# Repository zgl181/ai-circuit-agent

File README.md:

# AI Agent 电路板设计

> **给 AI 一句话，产出一块板子。**
> 输入自然语言需求（如「设计一个 LED 闪烁电路，1 个 LED、1 个限流电阻、1 个轻触按钮、1 个电池座」），
> 自动产出 **BOM 元件清单 + 引脚级网表 + KiCad 8 可直接打开的原理图**。

个人课程大作业（8 周项目制） · Python 3.10+ / KiCad 8 / LLM（OpenAI 兼容接口）

---

## 效果

一句需求 → 原理图 → PCB 全链路产物：

| 产物 | 说明 |
|---|---|
| `outputs/design.json` | 结构化设计：`{board, components[], nets[]}`（BOM + 引脚级连接） |
| `outputs/design.net` | KiCad 标准网表（可直接给 pcbnew 做布局） |
| `outputs/design.kicad_sch` | KiCad 8 原理图，**双击即可打开** |
| `outputs/design.svg` | 原理图预览图（用于网页展示 / 自动校验） |
| `outputs/design.kicad_pcb` | KiCad 8 **PCB 板文件**：真实官方封装 + 自动布局 + 双层走线 + 两层 GND 铺铜 |
| `outputs/board_routes.json` | 自动布线结果（每条走线的网络、层、折点、过孔） |
| `outputs/drc_report_summary.json` | DRC 闭环报告：每轮违规数 / 未连接数下降曲线与最终统计 |
| `outputs/pcb.svg` / `pcb_preview.png` | PCB 顶层装配视图（隐藏铜皮，便于看清元件与走线） |

原理图和 PCB 都会**自动通过 `kicad-cli` 反向校验**：前者反导网表逐引脚比对，后者跑 DRC 并用报告反向驱动布线，确认不是"只画了好看的线"。

> **W8 设计报告**：[`AI Agent 电路板设计-设计报告.docx`](./AI%20Agent%20电路板设计-设计报告.docx)——含封面、目录、页码、两张预览图与全部自检数据。正文九章 + 两个附录，覆盖需求架构、基础五步、进阶 PCB/DRC 闭环、六项自检、F1 语义错误案例、过程管理与 AI 使用声明。

## 功能特性

- **自然语言 → 结构化设计**：LLM 输出固定 JSON（BOM + 网表），带自检（位号引用一致性）
- **生成真实可用的 KiCad 8 原理图**：内嵌真实符号定义，文件自包含，无需额外库表
- **自适应论文式排版**：按元件类型与连接关系动态分组，只画实际用到的功能框（**空组一律不画**），框贴合内容、整体在 A4 内居中铺满；Arduino 完整版沿用人工验收的固定五分区。一键生成和每次微调都会重新排版，始终给出最好看的版面
- **正交自动布线 + 网络名标签**：先横后竖连线，网络名贴在导线中点
- **PCB 自动布局布线（进阶）**：26 个元件全部映射到 KiCad 官方封装，按 5 个功能分区 shelf-packing 排布，35 个网络逐焊盘绑定；双层 0.5mm 网格 A* 自动布线，自动打过孔换层
- **DRC 闭环（进阶）**：`kicad-cli pcb drc --format json` 报出「项目之间的连接缺失」→ 解析两个焊盘的精确坐标与网络名 → 自动补线 → 重跑 DRC，逐轮让未连接项下降
- **GND 铺铜**：F.Cu / B.Cu 全板敷铜，自动避让其它网络，一次性连通所有地焊盘
- **本地网页界面**：零前端框架，原理图 / PCB 预览一键切换，可下载 `.kicad_pcb`
- **MongoDB 后端（可选）**：设计历史、多用户登录、LLM 结果缓存、多 Agent 共享状态；**未安装 mongod 时自动退化为内存版 mongomock，照样能跑**
- **离线兜底（平台抖动也不停工）**：学校 LLM 不可达时 5 秒内自动切到内置模板（LED 闪烁 / 双 LED 流水灯 / 电池开关灯 / ATmega 最小系统），一键生成照常出图
- **交互修正（基础第五步）**：生成后可在结果页"追加要求"框直接说「再加一个 10k 电阻」「把 LED 换成绿色」「去掉按钮」，在当前电路上增删改并**自动重新排版**；LLM 不可用时走本地规则解析，照样能用
- **对话工作台（推荐，`/chat`）**：仿对话助手界面——**每次新建对话 = 一份独立电路**；第一条消息生成，之后在同一对话里反复改图，每轮都有快照。**不同对话之间完全隔离**：在 A 里加电阻、改颜色，B 新生成的仍是干净原始电路，互不污染
- **六项一键自检**：网表一致性 / ERC / 排版几何 / 导线穿模 / PCB 与 DRC 闭环 / 电源语义

## 技术架构

```
            自然语言需求
                 │
                 ▼
   scripts/design_agent.py  ── 5s 探测学校平台
                 │             ├─ 可达：LLM 输出严格 JSON（BOM + nets）
                 │             └─ 不可达：local_design.py 内置模板兜底
                 ▼
          design.json  {board, components[], nets[]}
          ┌──────┴───────────────────────┐
          ▼                              ▼
 scripts/kicad_net.py            scripts/kicad_sch.py
   → design.net (KiCad 网表)       → design.kicad_sch (KiCad 8 原理图)
                                          │
                                          ▼
                                   kicad-cli sch export svg  → design.svg
                                   kicad-cli sch export netlist → 连通性校验
```

网页层 `scripts/app.py` 把上面整条管线包成 HTTP 接口，`scripts/db.py` 提供 MongoDB 存储。

## 项目结构

```
.
├── scripts/
│   ├── design_agent.py     # 自然语言 -> BOM + 网表 JSON（真调 LLM）
│   ├── kicad_net.py        # JSON -> KiCad 网表 .net
│   ├── kicad_sch.py        # JSON -> KiCad 8 原理图 .kicad_sch（内嵌符号 + 正交布线）
│   ├── kicad_pcb.py        # JSON -> KiCad 8 PCB（官方封装 + 分区布局 + 走线 + 铺铜）
│   ├── drc_loop.py         # DRC 报告 -> 双层 A* 自动补线 -> 重跑 DRC 的闭环编排
│   ├── verify_schematic.py # 六项一键自检（原理图 A–D + PCB/DRC E + 电源语义 F）
│   ├── llm_client.py       # LLM 客户端（读取 .env，5s 可达性探测 + 重试）
│   ├── local_design.py     # LLM 不可达时的内置电路模板兜底
│   ├── local_refine.py     # 交互修正：离线规则解析「增/删/改」增量要求
│   ├── templates/          # 内置模板（已验收的 ATmega 最小系统 design.json）
│   ├── db.py               # MongoDB 数据层（自动退化 mongomock）
│   ├── app.py              # 本地网页服务（注册/登录/生成/历史/共享状态）
│   ├── web/index.html      # 旧版单页界面（/）
│   └── web/chat.html       # 对话工作台（/chat，推荐）
├── outputs/                # 生成产物（示例）
├── requirements.txt
├── .env.example            # 密钥模板（真实 .env 不进仓库）
├── 启动界面.bat             # Windows 一键启动网页界面
└── README.md
```

## 环境要求

- Python **3.10+**
- KiCad **8.x**（需要 `kicad-cli` 与符号库 `share/kicad/symbols`）
- LLM API：任何 **OpenAI 兼容**接口（本项目默认接学校平台）
- MongoDB **（可选）**：不装也能跑，走 mongomock 兜底

## 安装

```bash
git clone <你的仓库地址>
cd <仓库目录>

python -m venv .venv
.venv\Scripts\activate            # Windows
# source .venv/bin/activate       # macOS / Linux

pip install -r requirements.txt

# 配置密钥：复制模板后填写
copy .env.example .env             # Windows
# cp .env.example .env             # macOS / Linux
```

### `.env` 说明

```ini
LLM_API_KEY=你的密钥
LLM_BASE_URL=https://你的平台地址/v1
LLM_MODEL=你的模型名
```

### KiCad 路径（可选覆盖）

默认使用 Windows KiCad 8 安装路径；若你的安装位置不同，用环境变量覆盖即可：

```bash
set KICAD_SYM_DIR=D:\KiCad\8.0\share\kicad\symbols
set KICAD_CLI=D:\KiCad\8.0\bin\kicad-cli.exe
```

## 运行

### 方式一：命令行（三段管线）

```bash
# 1) 自然语言 -> 设计 JSON
python scripts/design_agent.py "设计一个 LED 闪烁电路，包含 1 个 LED、1 个限流电阻、1 个轻触按钮、1 个 2 节电池座"

# 2) JSON -> 网表
python scripts/kicad_net.py outputs/design.json outputs/design.net

# 3) JSON -> 原理图
python scripts/kicad_sch.py outputs/design.json outputs/design.kicad_sch
```

### 方式一（续）：PCB 与 DRC 闭环（进阶）

PCB 用 `pcbnew` Python API，**必须用 KiCad 自带的 Python 运行**（项目 `.venv` 里没有 pcbnew）：

```bash
# 4) JSON -> PCB（真实封装、分区布局、GND 铺铜）
"C:/Users/24013/Desktop/工具/bin/python.exe" scripts/kicad_pcb.py

# 5) DRC 闭环：自动布线 + 迭代校验，一步到位（内部会反复调用 4）
"C:/Users/24013/Desktop/工具/bin/python.exe" scripts/drc_loop.py --max-iter 7

# 6) 六项一键自检
python scripts/verify_schematic.py
```

KiCad 路径不同可用环境变量覆盖：`KICAD_FP_DIR`（封装库）、`KICAD_CLI`（命令行工具）。
`drc_loop.py` 会在最后一轮自动起一个独立进程填充铜皮，避开 pcbnew 在同一进程反复 zone fill 的段错误。

### 方式二：网页界面（推荐）

```bash
# 双击 启动界面.bat ；或手动：
.venv\Scripts\python.exe scripts\app.py
```

浏览器打开 <http://localhost:8765>：

1. 输入需求（或点示例）→ 点「生成原理图」
2. 页面直接显示 BOM 表格、网表、原理图预览
3. 可下载 `.kicad_sch` / `.net` / `.json`
4. 注册登录后，设计自动存入「我的设计历史」，可回看载入
5. 相同需求二次生成会**命中 LLM 缓存**，不再重复调用模型
6. 学校平台连不上时自动用内置模板出图（约 5 秒），不报错、不用改配置
7. **追加要求**：生成结果下方有「追加要求」框，输入「再加一个 10k 电阻」「去掉按钮」「把 R1 改成 1k」等，点「应用修改并重新排版」即可在当前电路上迭代，无需重写整段需求

> **对话工作台**（推荐）：访问 <http://localhost:8765/chat>。左侧「+ 新建对话」开一份独立电路，第一条消息生成，后续消息都在本对话里改图；每轮消息附**原理图 / PCB 双预览**（可切换）与 JSON / 网表 / `.kicad_sch` / `.kicad_pcb` / SVG 下载。生成过程有分阶段状态提示，不会让人误以为卡住。不同对话各自保存 design，互不影响——适合"一个需求一个对话、随便改"的用法。
>
> **对话记录持久化**：对话存在 `.workbuddy/chat_store.json`（独立于 MongoDB/mongomock），**服务重启、刷新页面都不丢**；点左侧「×」可删除单个对话。旧版单页仍在 `/`。

## MongoDB 后端（可选）

- **不装 mongod**：`db.py` 连不上本地 `mongodb://localhost:27017` 时自动使用 `mongomock`（内存），功能齐全但重启即清空。
- **装了 mongod**：启动服务时自动切到 `real` 模式，数据持久化。

### 本机已部署（便携版，无需管理员权限）

MongoDB 8.0 便携版已下载解压到本机，普通用户即可运行：

- 程序：`C:\Users\24013\Desktop\工具\mongodb\mongodb-win32-x86_64-windows-8.0.0\bin\mongod.exe`
- 数据目录：`C:\Users\24013\Desktop\工具\mongodb-data`（重启后数据仍在）
- 默认监听 `127.0.0.1:27017`，仅本机访问

启动方式（二选一）：

- **双击 `启动界面.bat`（推荐）**：先拉起 MongoDB，等几秒再开网页界面，一条龙。
- **双击 `start-mongo.bat`**：只启动 MongoDB（不启网页），便于单独调试。

> 装好并运行后，`scripts/db.py` 会自动从 `mongomock`（内存）切到 `real`（真 MongoDB），无需改任何代码。判断当前模式：启动后访问网页、注册/生成任意一次，或在 `scripts/` 下执行
> `.venv\Scripts\python.exe -c "import db; print(db.mode())"` 会打印 `real`。

集合设计（数据库 `circuit_agent`）：

| 集合 | 用途 |
|---|---|
| `users` | 账号（加盐 SHA-256 存密码哈希） |
| `sessions` | 登录 token |
| `designs` | 设计历史（按 owner 隔离） |
| `cache` | LLM 结果缓存（按 prompt 的 SHA-256 命中） |
| `agent_state` | 多 Agent 共享状态（键值） |

## 已验证

示例设计为 **Arduino 最小系统板**（ATmega328P-PU DIP-28 + CH340G USB 转串口），
26 个元件 / 35 个网络。一键自检：

```bash
python scripts/verify_schematic.py
```

该脚本校验六项，全部通过才返回退出码 0（可直接用于答辩演示或 CI）：

| 检查 | 方法 | 当前结果 |
| --- | --- | --- |
| A. 网表一致性 | `kicad-cli sch export netlist` 反导出的网表与 `design.json` 逐网络、逐引脚比对；并检测同一引脚落入多个网络（短路） | 35/35 一致，0 短路 |
| B. 电气规则 | 解析 `erc.txt`，统计 `; error` | 0 error（144 条为 `endpoint_off_grid` / `lib_symbol_issues` 提示，不影响电气） |
| C. 排版几何 | 解析 `.kicad_sch` **内嵌符号的真实引脚坐标**，检查元件重叠、标签压元件、标签互相叠字、超出 A4 图框 | 26 元件 / 108 标签，4 项均为 0 |
| D. 导线不穿模 | 逐段采样导线，检查其中段是否穿过任何元件本体（两端各跳过 4.5mm 引脚区） | 112 段导线，穿模 0 段 |
| E. PCB / DRC 闭环 | 检查板文件、走线、闭环报告齐备；设计规则违规必须为 0，且未连接项须比首轮明显下降 | 违规 0，未连接 58 → 22（223 段走线 / 25 过孔） |
| F. 电源语义 | 直接校验 `design.json` 的**供电逻辑**：保护/限流器件不得跨接电源与地，保险丝必须串联在两个不同的电源网络之间 | F1 = `USB_VBUS → +5V` 串联正确，异常跨接 0 |

> **为什么单列 F 项**：A–E 验的是「生成文件是否忠实于设计 JSON」。如果 LLM 一开始就把保险丝写成
> `+5V → GND`，图画得再准、ERC 与 DRC 也照样全绿。本项对设计意图做独立规则判断；
> 已用回归测试验证：把 F1 改回旧接法时 F 项会立即 FAIL。

原理图为 A4 横向（`viewBox = 297×210mm`），采用**论文插画式**版面：

- **5 个虚线功能分区 + 加粗小标题**（① 电源输入、② USB-UART/CH340G、③ MCU 核心、④ 去耦与 I/O 排针、⑤ 状态指示与复位），元件只在自己的框内排布，读图不必全屏搜索。
- **主控是左右对称的 DIP-28**：左侧 pin1–14、右侧 pin28–15，引脚名按数据手册（PC6/RESET、PD0/RXD…）标注，网络标签在两侧各排成整齐一列。官方库 `ATmega328P-P` 把 23 个脚全画在右侧，这里用自包含的对称符号替换（不动本机库）。
- **LED 支路是真正的串联**：限流电阻改用横放符号，与 LED 引脚同向，`D13 → R3 → LED_D13 → D2 → GND` 画成一条干净的水平线；中间的网络名标签抬到导线上方 1.8mm，用一小段竖线挂接（水平导线在分支点拆成两段以保证电气连通），文字不再被导线穿过。不再是"一条线穿过电阻本体"。
- 其余符号直接嵌入 KiCad 官方库的**原始图形**（电容双板、电阻、晶振、开关、排针等），不是空白矩形框；所有导线均为短正交直线 stub（无斜线），网络标签朝元件外侧展开，位号/数值文字按真实符号高度紧贴本体。右下角标题栏未被压住。

**两种排版路线**：`build_sch()` 先判断是否为 Arduino 完整版（ATmega328P + CH340G 且元件数 ≥18）——是则沿用上面这套人工验收的固定五分区（保证已交付产物零回归）；否则走 `adaptive_layout()`：按元件类型 + 连接关系动态分组、**只画实际有元件的框**，框大小贴合内容、整体在 A4 可用区（Y ≤168mm，避开标题栏）内居中铺满，列数从 1 到 4 自动扩展以适配不同规模。这样从 2 元件到 26 元件，一键生成和每次微调都能得到没有空框、不压标题栏的版面。回归验收：`2 / 6 / 12 / 26` 元件四种规模均渲染通过，官方版电气与几何事实与交付产物完全一致。

`kicad-cli sch export svg` 可正常导出，渲染预览见 `outputs/schematic_preview.png`。

## PCB 与 DRC 闭环（进阶项）

板框 140×62mm，26 个元件全部使用 KiCad 8 **官方封装**（DIP-28 / SOIC-16 / HC-49 / 0603 / Micro-USB / 排针等），
按原理图的 5 个功能分区做 shelf-packing 自动布局，35 个网络逐焊盘绑定（112 处，无遗漏）。

**闭环工作方式** —— 不是"画完线再跑一次 DRC"，而是让 DRC 报告反过来驱动布线：

1. `kicad-cli pcb drc --format json` 把「项目之间的连接缺失」逐条列出，每条都带**两个端点的精确坐标与网络名**；
2. 双层 0.5mm 网格 A* 在焊盘和已布走线之间找正交通路，其它网络一律视为障碍，必要时自动打过孔换层；
3. 把新走线写回板子，重跑 DRC，统计未连接项是否下降，直到不再有改善；
4. 最后一轮铺 F.Cu / B.Cu 两层 GND 铜皮（自动避让其它网络），把地网络一次性连通。

| 阶段 | 设计规则违规 | 未连接项 |
| --- | --- | --- |
| 初始（仅布局，无走线） | 0 | 78 |
| 铺 GND 铜皮后（地网络交由铜皮负责） | 0 | 58 |
| 自动布线迭代后 | 0 | 22 |
| 最终 | **0** | **22** |

最终板子含 **223 段走线 / 25 个过孔 / 2 层铜皮**，共 56 条连接由 Agent 自动完成。
剩余 22 条为待人工或外部布线器补的连接 —— **KiCad 8 没有命令行自动布线器，本机也未装 Freerouting**，
这是工具链的客观边界；`drc_report.json` 逐条列出了端点与网络，可直接在 pcbnew 里接着布。
顶层装配视图（隐藏铜皮以便看清元件）见 `outputs/pcb_preview.png`，网页可一键切换预览。

## 开发进度

- [x] W1 环境搭建（Python / KiCad / LLM 连通性自检）
- [x] W2 最小 Agent 调通学校 LLM：自然语言 → BOM JSON
- [x] W3 全链路：自然语言 → BOM + 网表 → **KiCad 8 原理图**
- [x] W4 论文式原理图版面（对称双列 MCU / 5 个功能分区）+ 原理图四项自检
- [x] 加分项：本地网页界面 + MongoDB 后端（历史 / 多用户 / 缓存 / 多 Agent 共享状态）+ PCB 预览切换
- [x] 进阶 ①：PCB 自动布局布线（官方封装 / 分区布局 / 双层 A* 走线 / GND 铺铜）
- [x] 进阶 ②：DRC 检查闭环（DRC 报告反向驱动补线，最终违规 0）
- [x] W5 复核与修正：全图/局部渲染人工验收，新增电源语义自检 [F]，修正 F1 短路接法与 LED 标签压线
- [ ] 进阶 ③：多 Agent 协作 / 仿真评测（未做）
- [x] W8 交付 ①：设计报告（`AI Agent 电路板设计-设计报告.docx`，九章 + 两个附录）
- [x] W8 交付 ②：答辩 PPT（`答辩PPT/答辩PPT.pptx`，10 页，蓝白学术风，含两张真实成果图与六项自检数据；源页 `答辩PPT/slides/*.slide`）
- [ ] W8 交付 ③：3–5 分钟演示视频

## 已知限制

- 原理图侧：已完成功能分区自动布局与全正交导线；除两条 LED 支路是**实连导线**外，其余同网络引脚
  靠同名 net label 表达电气连接（而非跨区铜线）。
- PCB 侧：已生成真实封装的板文件并完成双层自动布线，但 35 个网络中仍有 **22 条连接未布通**
  （KiCad 无 CLI 自动布线器、本机未装 Freerouting）。`drc_report.json` 逐条列出端点与网络，
  可在 pcbnew 里人工补线。设计规则违规为 0，即已布的线全部合规、无短路、无间距问题。
- USB1 采用 `USB_Micro-B_Wuerth_614105150721_Vertical`：常见 Molex-105017 封装有 8 个无网络
  屏蔽焊盘把 1–5 号信号脚围死，自动布线时线引不出来，故换成屏蔽焊盘不挡路的官方封装。
- 自恢复保险丝 F1 借用 1206 电阻封装占位（两焊盘，电气一致），未使用专用 PTC 封装。
  F1 串联在 `USB_VBUS`（USB1.1）与 `+5V`（系统电源）之间；早期版本误把 F1.2 接到 GND，
  形成「5V 经保险丝短到地」且 VBUS 绕过保险丝的错误，已修正并新增 [F] 电源语义自检防复发。
- 符号映射表有限：电阻 / 电容 / LED / 开关 / 晶振 / MCU(ATmega328P) / CH340G / 连接器等。
- 为论文式版面额外内嵌 3 个**自包含符号**：`ATmega328P-DIP28`（左右各 14 脚）、
  `Device:R_H`（横放电阻）、`Device:LED_R`（右向导通 LED）。其中 LED_R 采用
  `pin1=A(阳极) / pin2=K(阴极)` 的 0603 常见编号习惯，使 `电阻→LED→GND` 正向导通；
  节点号与 `design.json` 完全一致，只改符号语义与图形方向。
- 原理图内嵌的是**自包含的简化符号副本**：为让 ERC 专注于连接完整性，`power_in` 引脚统一
  归一化为 `passive`（不建模电源驱动链，故无需额外挂 PWR_FLAG）；电源网络的真实连接关系
  由 [A] 网表一致性校验逐节点兜底。此归一化只作用于嵌入副本，不改动本机 KiCad 库。
- 已通过 `kicad-cli sch erc`（原理图 0 error）与 `kicad-cli pcb drc`（PCB 0 违规）；尚未做仿真评测。
- 引脚级连接的正确性依赖 LLM 输出质量（已加位号自检 + 网表反导出比对 [A] + 电源语义规则 [F] 兜底）。
  注意 [A] 只能证明「画出来的和写进去的一致」，电路逻辑是否合理仍须由 [F] 之类的语义规则独立判断。

## 学术诚信与 AI 使用声明

- 本项目在 AI 辅助下完成，AI 参与代码编写与文档整理；关键设计决策（架构、Prompt、坐标变换、KiCad 文件格式）均经本人理解与实测验证，可口头解释。
- 未使用他人项目代码；架构思路为"自然语言 → 结构化中间产物 → CAD 文件"的通用管线。
- 参考的课程模板 / 开源资料在下方致谢注明。

## 致谢

- 课程模板工程：`<填课程提供的仓库/来源>`
- KiCad 官方符号库与 `kicad-cli` 文档
- 学校大模型平台（OpenAI 兼容接口）

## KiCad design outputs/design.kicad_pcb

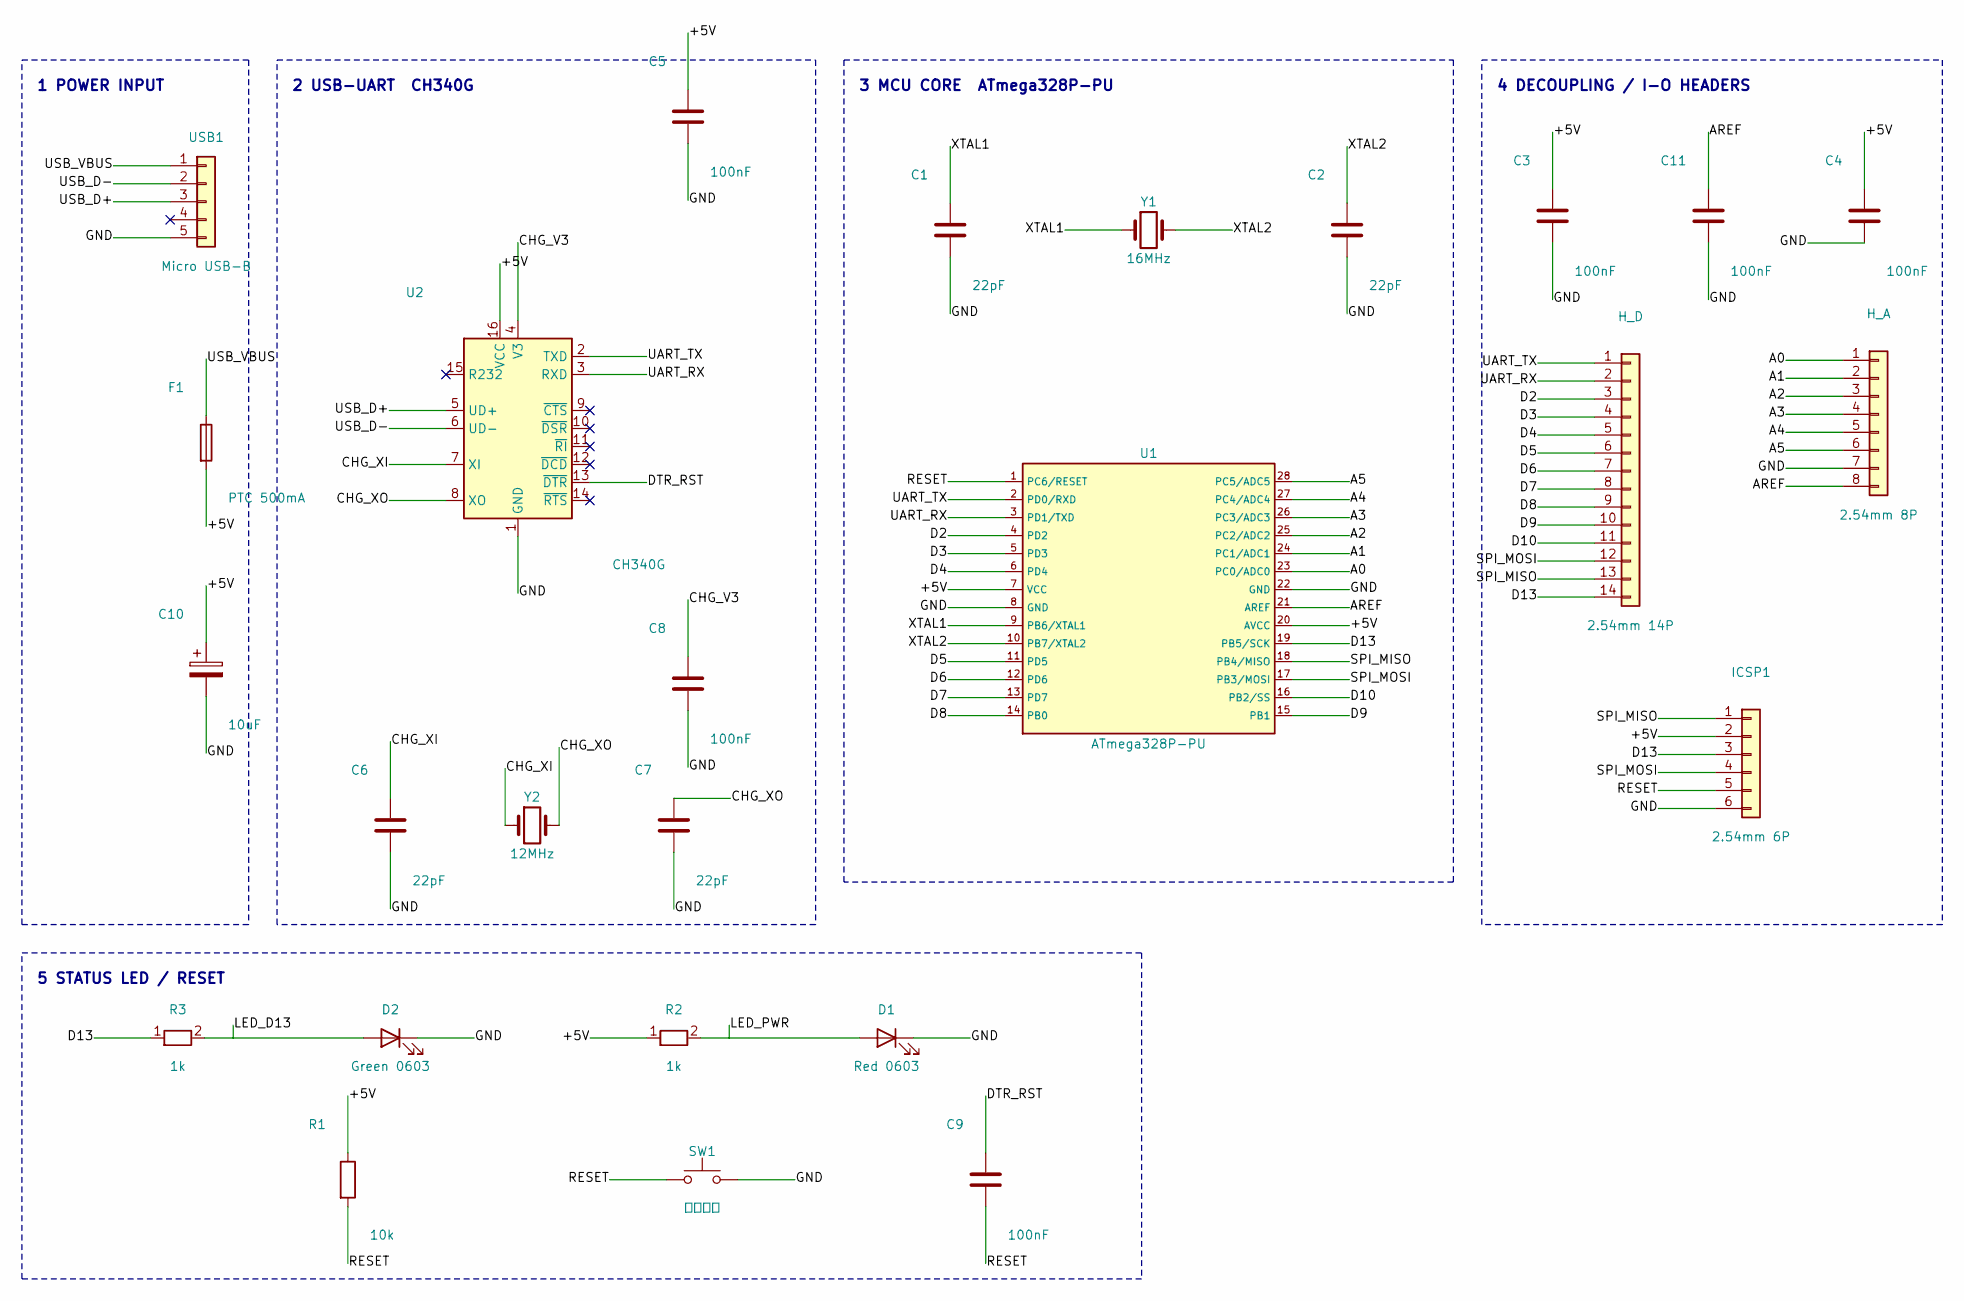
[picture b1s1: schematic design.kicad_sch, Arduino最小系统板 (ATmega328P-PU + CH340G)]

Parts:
C1, C2, C6, C7: 22pF; C0603
C3, C4, C5, C8, C9, C11: 100nF; C0603
C10: 10uF; Electrolytic
D1: Red 0603; LED-0603
D2: Green 0603; LED-0603
F1: PTC 500mA; SMD1206
H_A: 2.54mm 8P; HDR-8
H_D: 2.54mm 14P; HDR-14
ICSP1: 2.54mm 6P; HDR-6
R1: 10k; R0603
R2, R3: 1k; R0603
SW1: 复位按键; 6x6x5
U1: ATmega328P-PU; DIP-28
U2: CH340G; SOP-16
USB1: Micro USB-B; USB-MICRO-B-SMD
Y1: 16MHz; HC-49/US
Y2: 12MHz; HC-49/US

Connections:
+5V: C3.1, C4.1, C5.1, C10.1, F1.2, ICSP1.2, R1.1, R2.1, U1.7 (VCC), U1.20 (AVCC), U2.16 (VCC)
A0: H_A.1, U1.23 (PC0/ADC0)
A1: H_A.2, U1.24 (PC1/ADC1)
A2: H_A.3, U1.25 (PC2/ADC2)
A3: H_A.4, U1.26 (PC3/ADC3)
A4: H_A.5, U1.27 (PC4/ADC4)
A5: H_A.6, U1.28 (PC5/ADC5)
AREF: C11.1, H_A.8, U1.21 (AREF)
CHG_V3: C8.1, U2.4 (V3)
CHG_XI: C6.1, U2.7 (XI), Y2.1
CHG_XO: C7.1, U2.8 (XO), Y2.2
D2: H_D.3, U1.4 (PD2)
D3: H_D.4, U1.5 (PD3)
D4: H_D.5, U1.6 (PD4)
D5: H_D.6, U1.11 (PD5)
D6: H_D.7, U1.12 (PD6)
D7: H_D.8, U1.13 (PD7)
D8: H_D.9, U1.14 (PB0)
D9: H_D.10, U1.15 (PB1)
D10: H_D.11, U1.16 (PB2/SS)
D13: H_D.14, ICSP1.3, R3.1, U1.19 (PB5/SCK)
DTR_RST: C9.1, U2.13 (~DTR)
GND: C1.2, C2.2, C3.2, C4.2, C5.2, C6.2, C7.2, C8.2, C10.2, C11.2, D1.2 (K), D2.2 (K), H_A.7, ICSP1.6, SW1.2, U1.8 (GND), U1.22 (GND), U2.1 (GND), USB1.5
LED_D13: D2.1 (A), R3.2
LED_PWR: D1.1 (A), R2.2
RESET: C9.2, ICSP1.5, R1.2, SW1.1, U1.1 (PC6/RESET)
SPI_MISO: H_D.13, ICSP1.1, U1.18 (PB4/MISO)
SPI_MOSI: H_D.12, ICSP1.4, U1.17 (PB3/MOSI)
UART_RX: H_D.2, U1.3 (PD1/TXD), U2.3 (RXD)
UART_TX: H_D.1, U1.2 (PD0/RXD), U2.2 (TXD)
USB_D+: U2.5 (UD+), USB1.3
USB_D-: U2.6 (UD-), USB1.2
USB_VBUS: F1.1, USB1.1
XTAL1: C1.1, U1.9 (PB6/XTAL1), Y1.1
XTAL2: C2.1, U1.10 (PB7/XTAL2), Y1.2

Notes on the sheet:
1 POWER INPUT
2 USB-UART CH340G
3 MCU CORE ATmega328P-PU
4 DECOUPLING / I-O HEADERS
5 STATUS LED / RESET

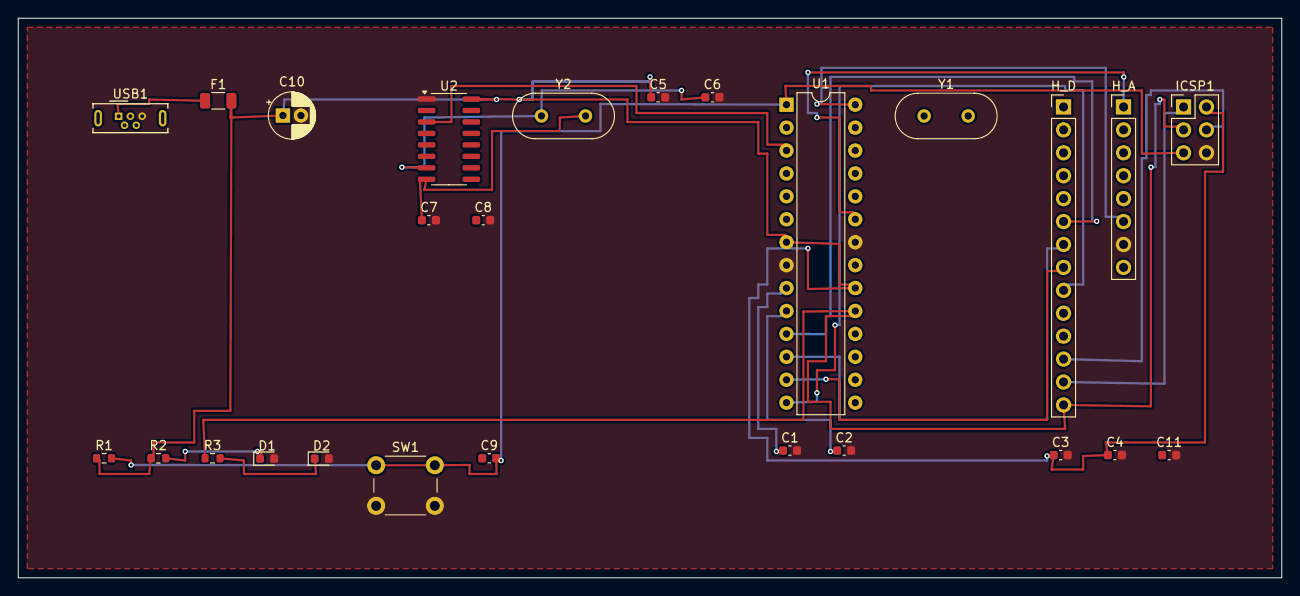
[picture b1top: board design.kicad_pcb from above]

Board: 2 copper layers, 140.0 x 62.0 mm, 26 parts (0 on the bottom side), 35 nets.

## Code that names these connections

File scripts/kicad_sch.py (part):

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# 这里按 DIP-28 真实封装重画一个左右各 14 脚的对称符号（自包含嵌入，不动本机库）。
# ---------------------------------------------------------------------------
DIP28_PIN_NAMES = {
    1: "PC6/RESET", 2: "PD0/RXD", 3: "PD1/TXD", 4: "PD2", 5: "PD3", 6: "PD4",
    7: "VCC", 8: "GND", 9: "PB6/XTAL1", 10: "PB7/XTAL2", 11: "PD5", 12: "PD6",
    13: "PD7", 14: "PB0", 15: "PB1", 16: "PB2/SS", 17: "PB3/MOSI",
    18: "PB4/MISO", 19: "PB5/SCK", 20: "AVCC", 21: "AREF", 22: "GND",
    23: "PC0/ADC0", 24: "PC1/ADC1", 25: "PC2/ADC2", 26: "PC3/ADC3",
    27: "PC4/ADC4", 28: "PC5/ADC5",
}


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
